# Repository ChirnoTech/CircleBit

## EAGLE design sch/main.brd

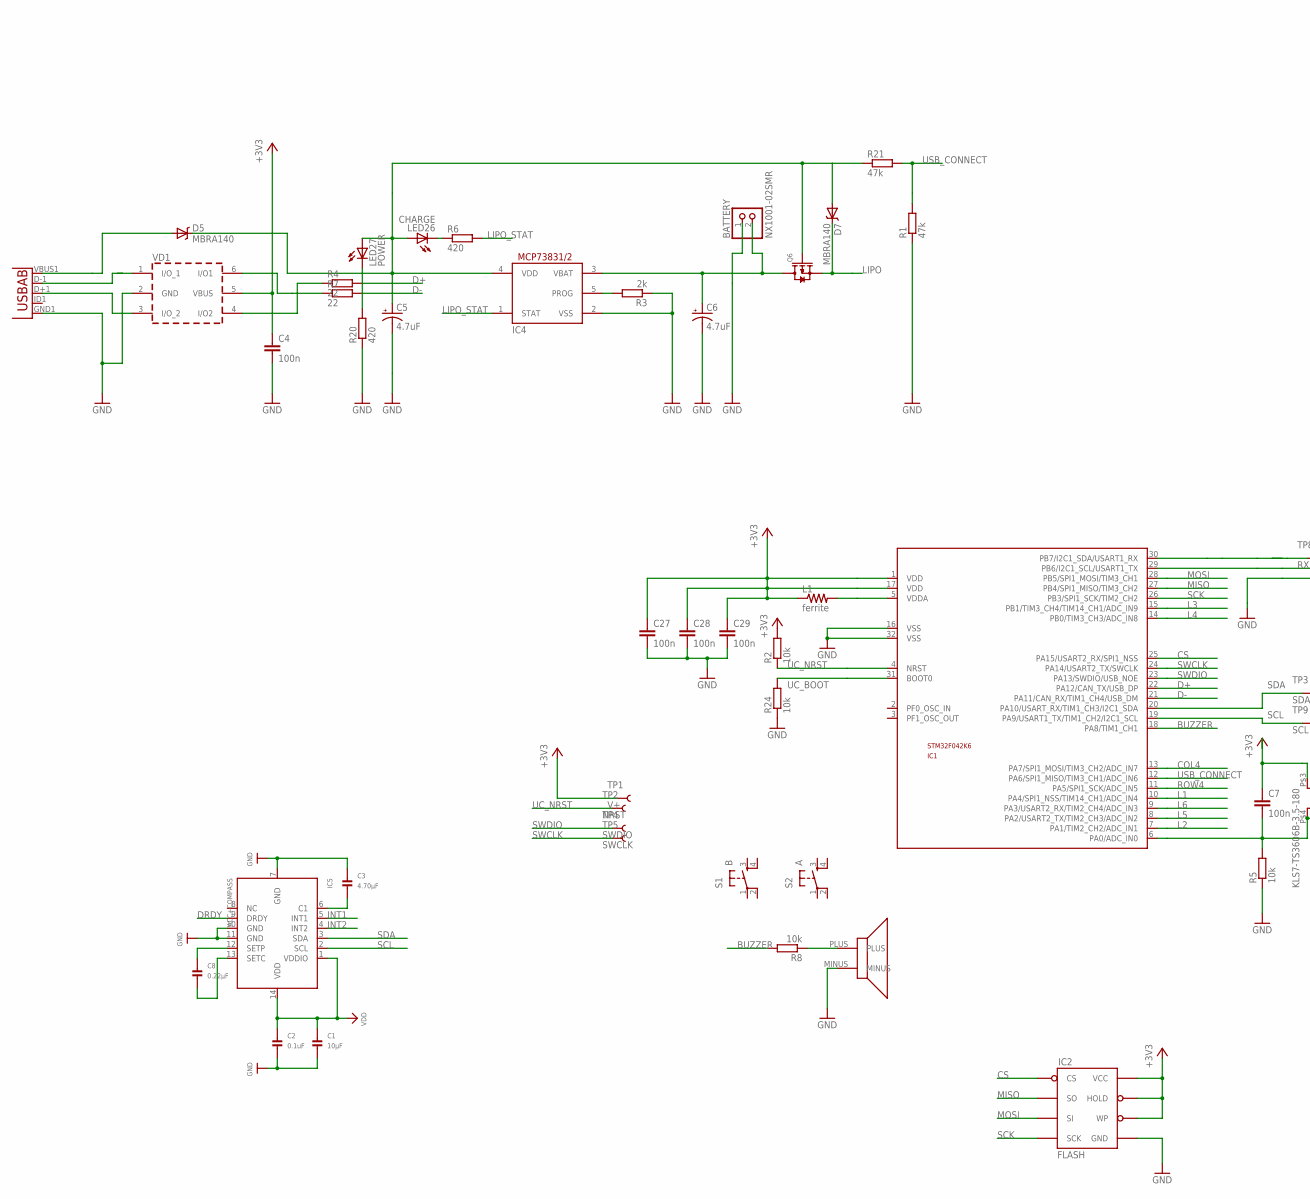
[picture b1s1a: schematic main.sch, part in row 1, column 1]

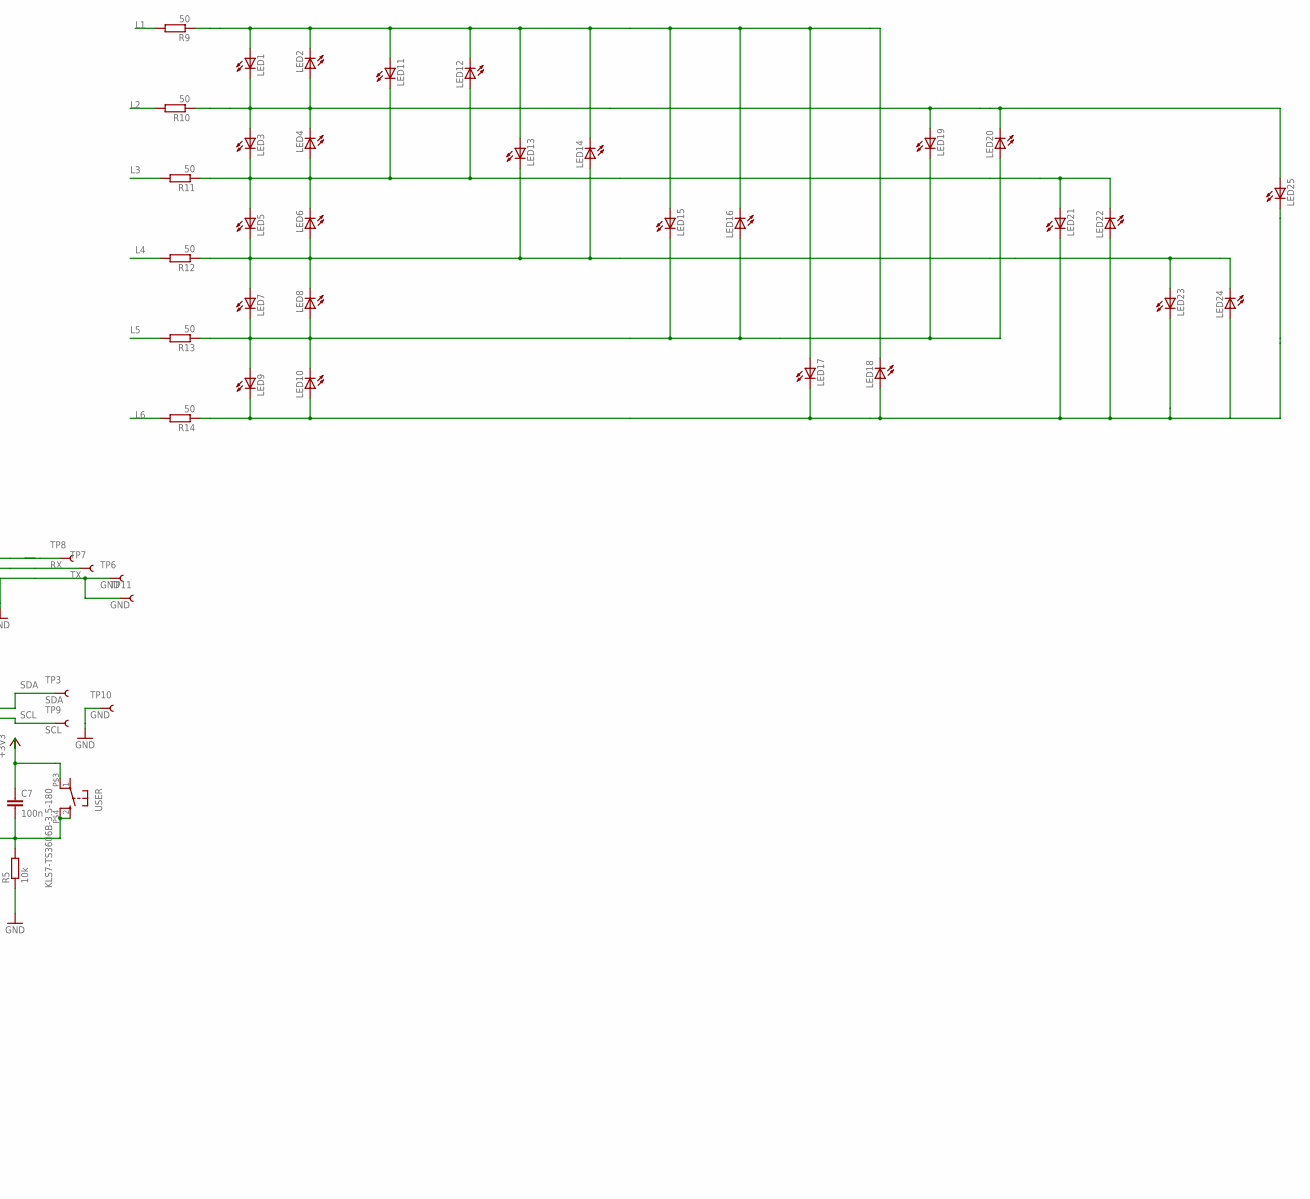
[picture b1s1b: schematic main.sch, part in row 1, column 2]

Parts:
BATTERY: NX1001-02SMR; NX1001-02
C1: 10µF; _0805
C2: 0.1uF; _0805
C3: 4.70µF; _0805
C4, C7, C27, C28, C29: 100n; C0603
C5, C6: 4.7uF; EIA3216
C8: 0.22µF; _0805
D5, D7: MBRA140; SMA-DIODE
IC1: STM32F042K6; LQFP32-7X7
IC2: FLASH; SO08
IC4: MCP73831; SOT23-5L
IC5: ACC+COMPASS; LGA14
L1: ferrite; 0603-RES
LED1, LED2, LED3, LED4, LED5, LED6, LED7, LED8, LED9, LED10, LED11, LED12, LED13, LED14, LED15, LED16, LED17, LED18, LED19, LED20, LED21, LED22, LED23, LED24, LED25: LED_ESML0603; LED_SML0603
LED26: CHARGE; CHIP-LED0805
LED27: POWER; CHIP-LED0805
Q6: MOSFET-P-044021001; SOT23
R1, R21: 47k; R0603
R2, R5, R8, R24: 10k; R0603
R3: 2k; R0603
R4, R7: 22; R0603
R6, R20: 420; R0603
R9, R10, R11, R12, R13, R14: 50; R0603
S1: B; DTSM-6
S2: A; DTSM-6
TP1: V+; PAD.03X.05
TP2: NRST; PAD.03X.05
TP3: SDA; PAD.03X.05
TP4: SWDIO; PAD.03X.05
TP5: SWCLK; PAD.03X.05
TP6, TP10, TP11: GND; PAD.03X.05
TP7: TX; PAD.03X.05
TP8: RX; PAD.03X.05
TP9: SCL; PAD.03X.05
U2: USB""; USB-MICRO-SMD
U$1: SMD-090045F-03627; SMD090045F
USER: KLS7-TS3606B-3.5-180; KLS7-TS3606B
VD1: USBLC6-2SC6; SOT-23-6L

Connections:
+3V3: C4.1, C7.1, C27.1, C28.1, C29.1, IC1.1 (VDD), IC1.17 (VDD), IC2.3 (WP), IC2.7 (HOLD), IC2.8 (VCC), L1.1, R2.2, TP1.P$1, USER.P$3 (2), VD1.5 (VBUS)
BBBB: BATTERY.2, C6.A (+), IC4.3 (VBAT), Q6.3 (D)
BUZZER: IC1.18 (PA8/TIM1_CH1), R8.2
COL4: IC1.13 (PA7/SPI1_MOSI/TIM3_CH2/ADC_IN7)
CS: IC1.25 (PA15/USART2_RX/SPI1_NSS), IC2.1 (CS)
D+: IC1.22 (PA12/CAN_TX/USB_DP), R4.2
D-: IC1.21 (PA11/CAN_RX/TIM1_CH4/USB_DM), R7.2
DRDY: IC5.9 (DRDY)
GND: BATTERY.1, C1.2, C2.2, C3.1, C4.2, C5.C (-), C6.C (-), C27.2, C28.2, C29.2, IC1.16 (VSS), IC1.32 (VSS), IC2.4 (GND), IC4.2 (VSS), IC5.7 (GND), IC5.10 (GND), IC5.11 (GND), R1.1, R3.1, R5.1, R20.1, R24.1, TP6.P$1, TP10.P$1, TP11.P$1, U2.GND1 (GND), U$1.MINUS, VD1.2 (GND)
INT1: IC5.5 (INT1)
INT2: IC5.4 (INT2)
L1: IC1.10 (PA4/SPI1_NSS/TIM14_CH1/ADC_IN4), R9.2
L2: IC1.7 (PA1/TIM2_CH2/ADC_IN1), R10.2
L3: IC1.15 (PB1/TIM3_CH4/TIM14_CH1/ADC_IN9), R11.2
L4: IC1.14 (PB0/TIM3_CH3/ADC_IN8), R12.2
L5: IC1.8 (PA2/USART2_TX/TIM2_CH3/ADC_IN2), R13.2
L6: IC1.9 (PA3/USART2_RX/TIM2_CH4/ADC_IN3), R14.2
LIPO: D7.C, Q6.2 (S)
LIPO_STAT: IC4.1 (STAT), R6.2
MISO: IC1.27 (PB4/SPI1_MISO/TIM3_CH2), IC2.2 (SO)
MOSI: IC1.28 (PB5/SPI1_MOSI/TIM3_CH1), IC2.5 (SI)
unnamed: R8.1, U$1.PLUS
unnamed: U2.D-1 (D-), VD1.1 (I/O_1)
unnamed: U2.D+1 (D+), VD1.3 (I/O_2)
unnamed: C3.2, IC5.6 (C1)
unnamed: C8.1, IC5.12 (SETP)
unnamed: C8.2, IC5.13 (SETC)
unnamed: IC4.5 (PROG), R3.2
unnamed: LED1.A, LED2.C, LED11.A, LED12.C, LED13.A, LED14.C, LED15.A, LED16.C, LED17.A, LED18.C, R9.1
unnamed: LED1.C, LED2.A, LED3.A, LED4.C, LED19.A, LED20.C, LED25.A, R10.1
unnamed: LED3.C, LED4.A, LED5.A, LED6.C, LED11.C, LED12.A, LED21.A, LED22.C, R11.1
unnamed: D5.A, U2.VBUS1 (VBUS)
unnamed: IC1.29 (PB6/I2C1_SCL/USART1_TX), TP7.P$1
unnamed: IC1.5 (VDDA), L1.2
unnamed: R7.1, VD1.6 (I/O1)
unnamed: LED26.C, R6.1
unnamed: LED5.C, LED6.A, LED7.A, LED8.C, LED13.C, LED14.A, LED23.A, LED24.C, R12.1
unnamed: R4.1, VD1.4 (I/O2)
unnamed: LED7.C, LED8.A, LED9.A, LED10.C, LED15.C, LED16.A, LED19.C, LED20.A, R13.1
unnamed: LED27.C, R20.2
unnamed: LED9.C, LED10.A, LED17.C, LED18.A, LED21.C, LED22.A, LED23.C, LED24.A, LED25.C, R14.1
unnamed: C5.A (+), D5.C, D7.A, IC4.4 (VDD), LED26.A, LED27.A, Q6.1 (G), R21.1
ROW4: IC1.11 (PA5/SPI1_SCK/ADC_IN5)
RX: IC1.30 (PB7/I2C1_SDA/USART1_RX), TP8.P$1
SCK: IC1.26 (PB3/SPI1_SCK/TIM2_CH2), IC2.6 (SCK)
SCL: IC1.19 (PA9/USART1_TX/TIM1_CH2/I2C1_SCL), IC5.2 (SCL), TP9.P$1
SDA: IC1.20 (PA10/USART_RX/TIM1_CH3/I2C1_SDA), IC5.3 (SDA), TP3.P$1
SWCLK: IC1.24 (PA14/USART2_TX/SWCLK), TP5.P$1
SWDIO: IC1.23 (PA13/SWDIO/USB_NOE), TP4.P$1
UC_BOOT: IC1.31 (BOOT0), R24.2
UC_NRST: IC1.4 (NRST), R2.1, TP2.P$1
USB_CONNECT: IC1.12 (PA6/SPI1_MISO/TIM3_CH1/ADC_IN6), R1.2, R21.2
VDD: C1.1, C2.1, IC5.1 (VDDIO), IC5.14 (VDD)
WAKE_UP: C7.2, IC1.6 (PA0/ADC_IN0), R5.2, USER.2 (3), USER.P$4 (4)

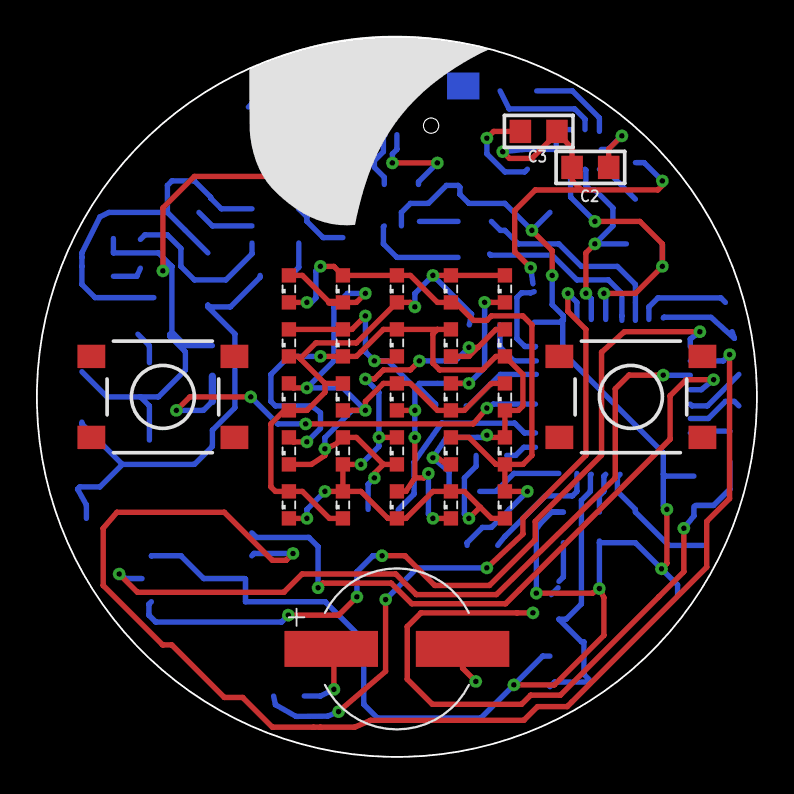
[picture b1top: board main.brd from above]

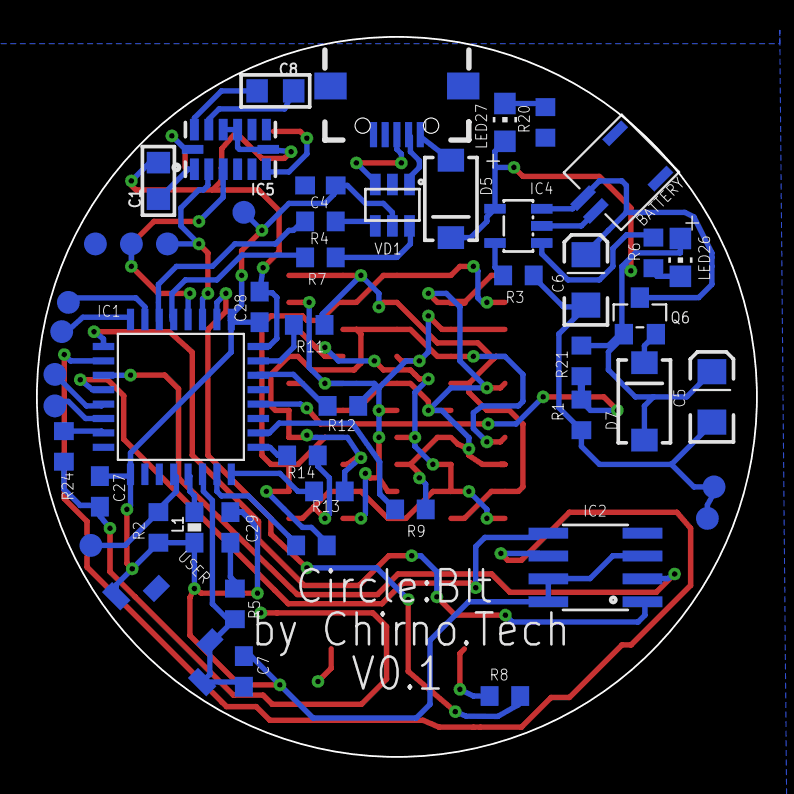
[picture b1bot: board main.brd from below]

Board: 2 copper layers, 40.0 x 40.0 mm, 81 parts (51 on the bottom side), 49 nets.

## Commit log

2016-12-01 Add schematics.

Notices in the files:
parts and their libraries:
SparkFun-Passives: Licensing: CC v3.0 Share-Alike You are welcome to use this library for commercial purposes.
microbuilder: This work is placed in the public domain, and may be freely used for commercial and non-commercial work with the following conditions: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
